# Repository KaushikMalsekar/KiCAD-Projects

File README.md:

# KiCAD-Projects
ECAD based Projects
Esp-12E

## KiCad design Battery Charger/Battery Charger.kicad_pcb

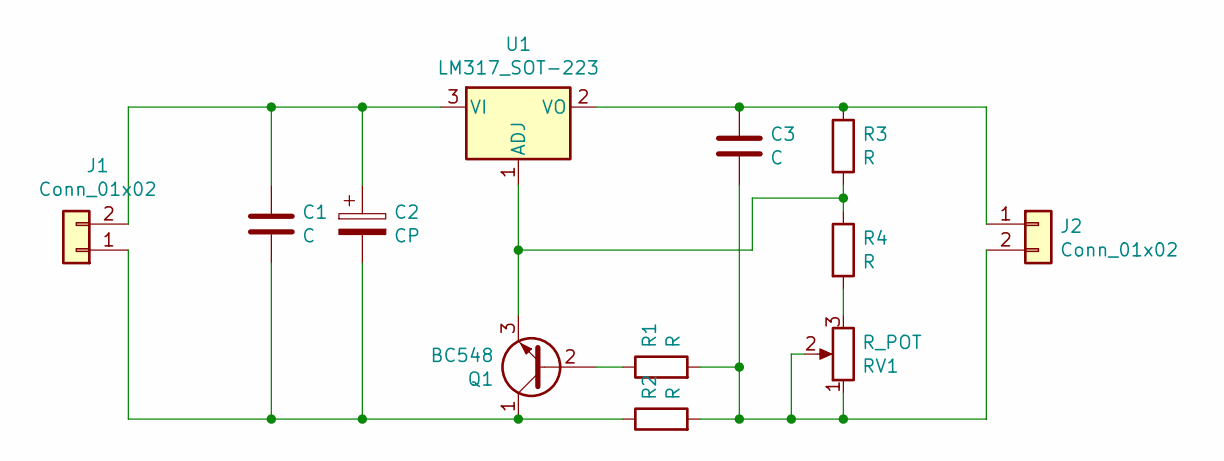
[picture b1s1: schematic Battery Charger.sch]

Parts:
C1, C3: C; C_Disc_D4.3mm_W1.9mm_P5.00mm
C2: CP; CP_Radial_D5.0mm_P2.50mm
J1, J2: Conn_01x02; JWT_A3963_1x02_P3.96mm_Vertical
Q1: BC548; TO-92_Inline
R1, R2, R3, R4: R; R_Axial_DIN0204_L3.6mm_D1.6mm_P1.90mm_Vertical
RV1: R_POT; Potentiometer_Bourns_3214G_Horizontal
U1: LM317_SOT-223; SOT-223-3_TabPin2

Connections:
unnamed: C1.1, C2.1, J1.2, U1.3 (VI)
unnamed: C1.2, C2.2, J1.1, Q1.1 (C), R2.1
unnamed: C3.1, J2.1, R3.1, U1.2 (VO)
unnamed: C3.2, J2.2, R1.2, R2.2, RV1.1, RV1.2
unnamed: Q1.2 (B), R1.1
unnamed: Q1.3 (E), R3.2, R4.1, U1.1 (ADJ)
unnamed: R4.2, RV1.3

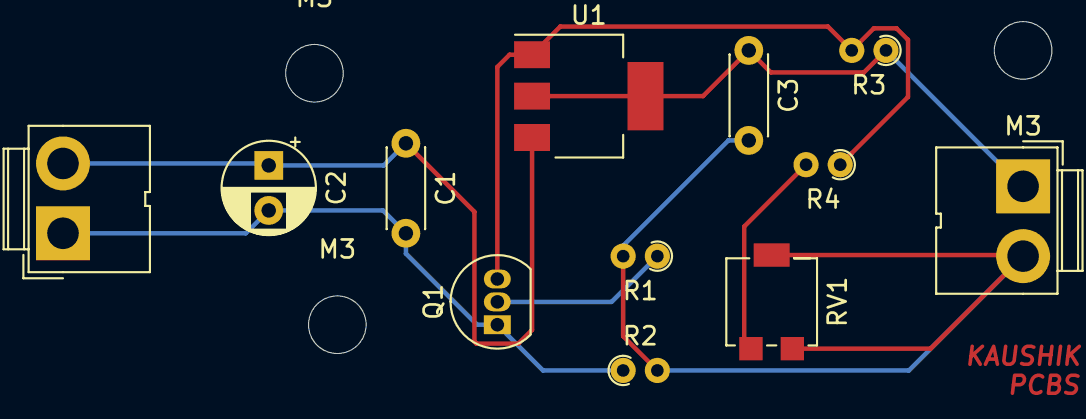
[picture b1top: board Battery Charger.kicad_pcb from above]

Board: 2 copper layers, 15 parts (0 on the bottom side), 7 nets.

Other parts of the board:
M3, M3#2, M3#3: MountingHole_3.2mm_M3

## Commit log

2021-08-04 Create ESP-12E
2021-08-04 Create new
